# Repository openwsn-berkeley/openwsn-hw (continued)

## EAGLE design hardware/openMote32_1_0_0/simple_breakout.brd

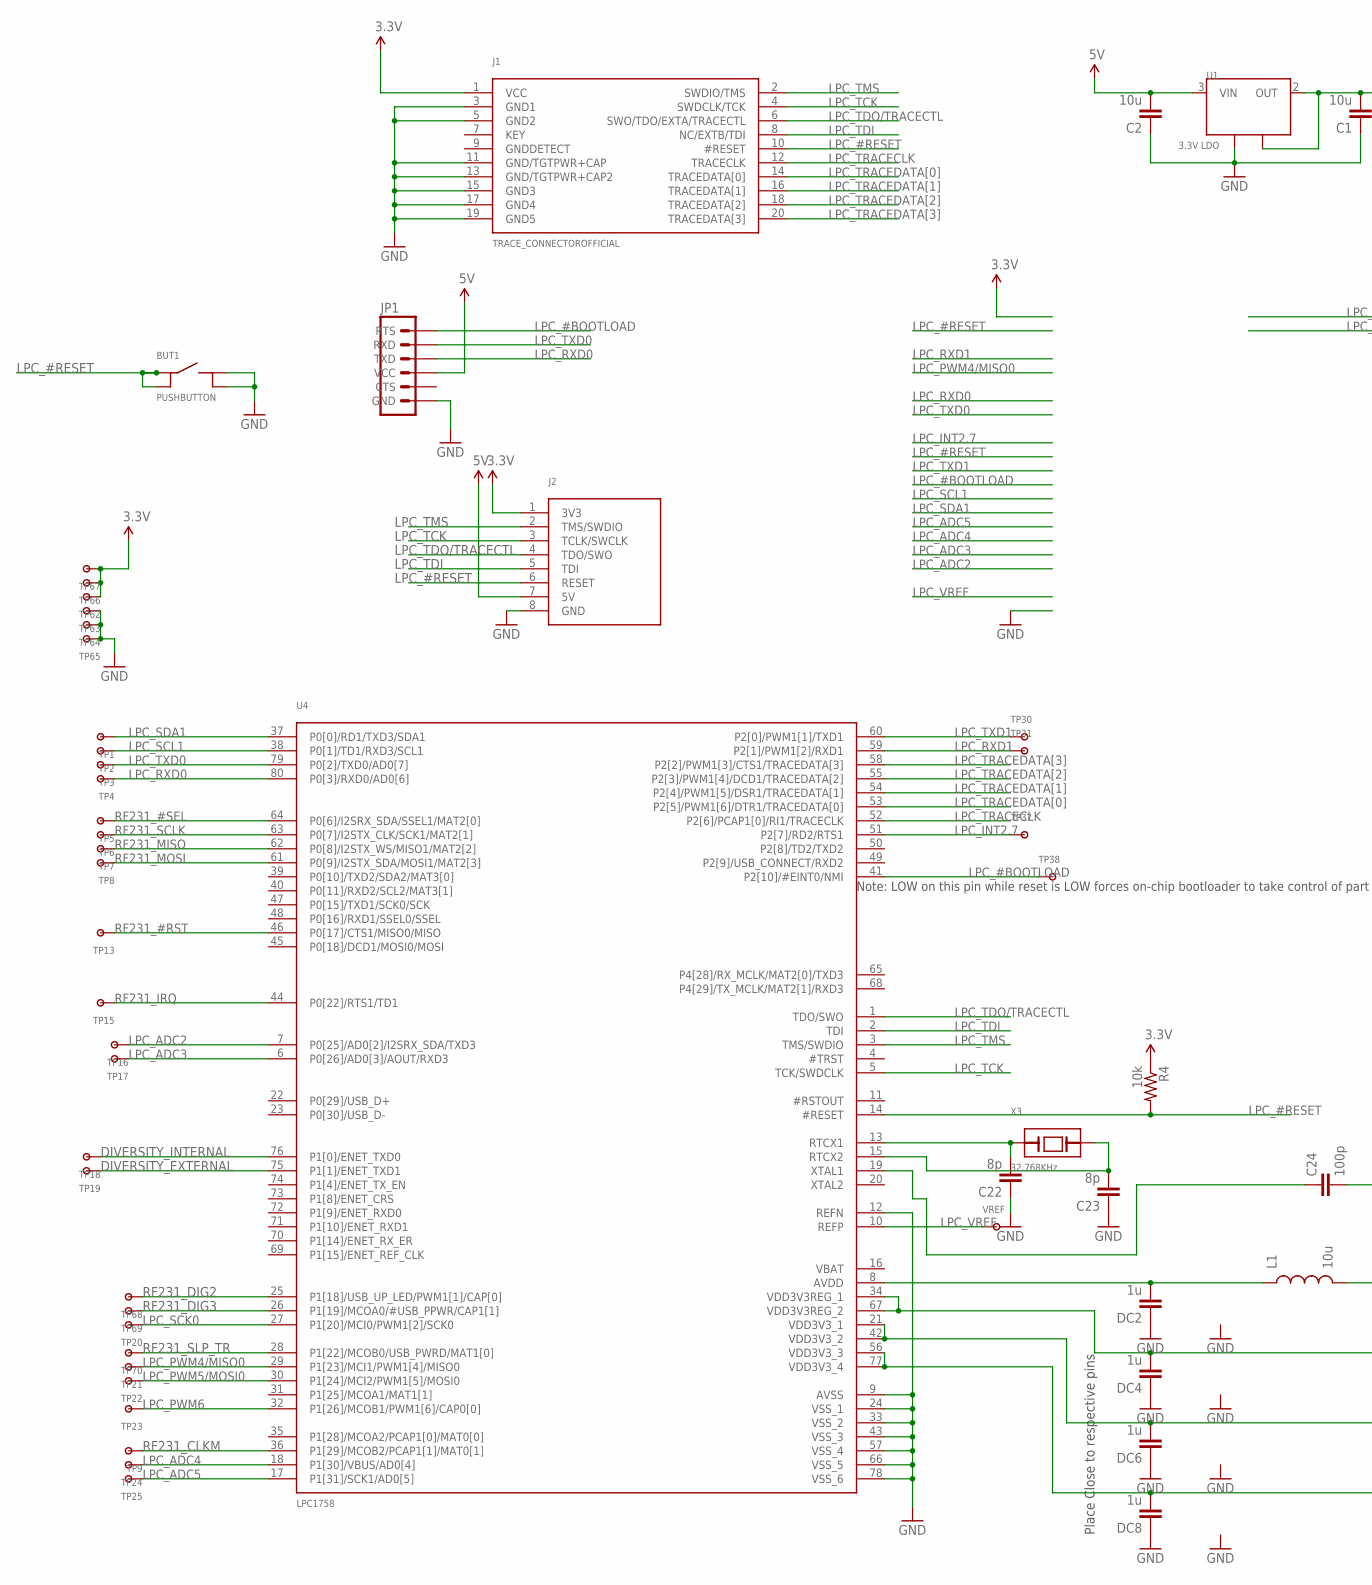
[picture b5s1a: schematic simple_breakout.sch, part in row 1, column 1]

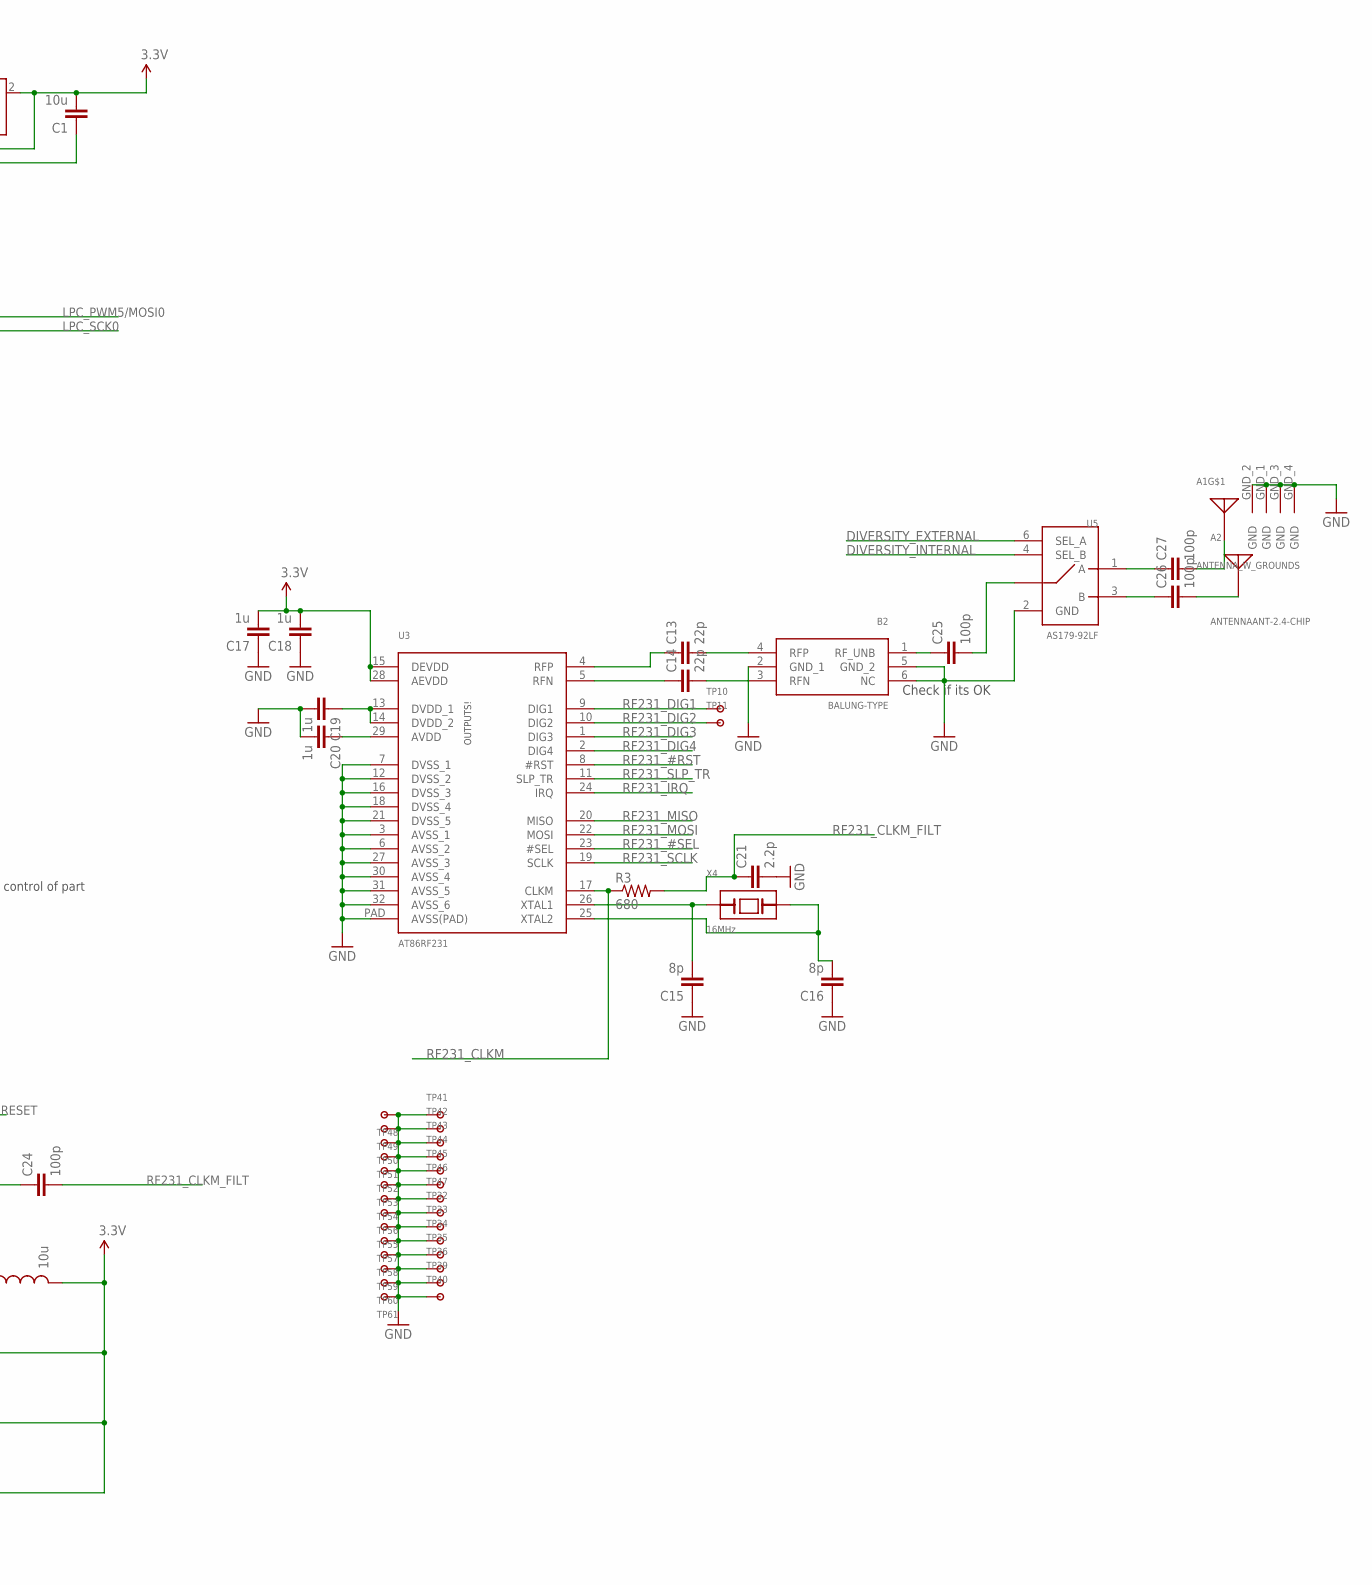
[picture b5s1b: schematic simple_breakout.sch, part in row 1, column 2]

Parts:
A1: ANTENNA_W_GROUNDS; CONREVSMA003.031
A2: ANTENNAANT-2.4-CHIP; ANT-2.4-CHP
B2: BALUNG-TYPE; MURATA_LDB_BALUN
BUT1: PUSHBUTTON; SMT_PUSHBUTTON
C1, C2: 10u; 0805
C13, C14: 22p; C0402
C15, C16, C22, C23: 8p; C0402
C17, C18, C19, C20: 1u; C0402
C21: 2.2p; C0402
C24, C25, C26, C27: 100p; C0402
DC2, DC4, DC6, DC8: 1u; C0402
J1: TRACE_CONNECTOROFFICIAL; FTSH-110-01-L-DV
J2: LPCXPRESSO_JTAG; 1X08
JP1: FTDI_CABLESIP; 1X06
L1: 10u; 0603
R3: 680; C0402
R4: 10k; C0402
TP1, TP2, TP3, TP4, TP5, TP6, TP7, TP8, TP9, TP10, TP11, TP13, TP15, TP16, TP17, TP18, TP19, TP20, TP21, TP22, TP23, TP24, TP25, TP30, TP31, TP37, TP38, TP62, TP63, TP64, TP65, TP66, TP67, TP68, TP69, TP70: TESTPOINT100MIL; TESTPOINT-100MIL
TP32, TP33, TP34, TP35, TP36, TP39, TP40, TP41, TP42, TP43, TP44, TP45, TP46, TP47, TP48, TP49, TP50, TP51, TP52, TP53, TP54, TP55, TP56, TP57, TP58, TP59, TP60, TP61: TESTPOINTSMALLEST; TESTPOINT
U1: 3.3V LDO; SOT223
U3: AT86RF231; ATRF231_32QN2
U4: LPC1758; LPC1758_LQFP80
U5: AS179-92LF; SC-70
VREF: TESTPOINT100MIL; TESTPOINT-100MIL
X3: 32.768KHz; ABS07
X4: 16MHz; CX3225SA

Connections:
3.3V: C1.2, C17.2, C18.2, DC4.2, DC6.2, DC8.2, J1.1 (VCC), J2.1 (3V3), L1.2, R4.1, TP62.2, TP66.2, TP67.2, U1.2 (OUT), U1.4 (TAB), U3.15 (DEVDD), U3.28 (AEVDD), U4.21 (VDD3V3_1), U4.34 (VDD3V3REG_1), U4.42 (VDD3V3_2), U4.56 (VDD3V3_3), U4.67 (VDD3V3REG_2), U4.77 (VDD3V3_4)
5V: C2.2, J2.7 (5V), JP1.3 (VCC), U1.3 (VIN)
DIVERSITY_EXTERNAL: TP19.2, U4.75 (P1[1]/ENET_TXD1), U5.6 (SEL_A)
DIVERSITY_INTERNAL: TP18.2, U4.76 (P1[0]/ENET_TXD0), U5.4 (SEL_B)
GND: A1.GND_1 (GND), A1.GND_2 (GND), A1.GND_3 (GND), A1.GND_4 (GND), B2.2 (GND_1), B2.5 (GND_2), B2.6 (NC), BUT1.2@1 (2), BUT1.2@2 (2), C1.1, C2.1, C15.1, C16.1, C17.1, C18.1, C19.2, C20.2, C21.2, C22.1, C23.1, DC2.1, DC4.1, DC6.1, DC8.1, J1.3 (GND1), J1.5 (GND2), J1.11 (GND/TGTPWR+CAP), J1.13 (GND/TGTPWR+CAP2), J1.15 (GND3), J1.17 (GND4), J1.19 (GND5), J2.8 (GND), JP1.1 (GND), TP32.P$1, TP33.P$1, TP34.P$1, TP35.P$1, TP36.P$1, TP39.P$1, TP40.P$1, TP41.P$1, TP42.P$1, TP43.P$1, TP44.P$1, TP45.P$1, TP46.P$1, TP47.P$1, TP48.P$1, TP49.P$1, TP50.P$1, TP51.P$1, TP52.P$1, TP53.P$1, TP54.P$1, TP55.P$1, TP56.P$1, TP57.P$1, TP58.P$1, TP59.P$1, TP60.P$1, TP61.P$1, TP63.2, TP64.2, TP65.2, U1.1 (GND), U3.3 (AVSS_1), U3.6 (AVSS_2), U3.7 (DVSS_1), U3.12 (DVSS_2), U3.16 (DVSS_3), U3.18 (DVSS_4), U3.21 (DVSS_5), U3.27 (AVSS_3), U3.30 (AVSS_4), U3.31 (AVSS_5), U3.32 (AVSS_6), U3.PAD (AVSS(PAD)), U4.9 (AVSS), U4.12 (REFN), U4.24 (VSS_1), U4.33 (VSS_2), U4.43 (VSS_3), U4.57 (VSS_4), U4.66 (VSS_5), U4.78 (VSS_6), U5.2 (GND)
LPC_#BOOTLOAD: JP1.6 (RTS), TP38.2, U4.41 (P2[10]/#EINT0/NMI)
LPC_#RESET: BUT1.1@1 (1), BUT1.1@2 (1), J1.10 (#RESET), J2.6 (RESET), R4.2, U4.14 (#RESET)
LPC_ADC2: TP16.2, U4.7 (P0[25]/AD0[2]/I2SRX_SDA/TXD3)
LPC_ADC3: TP17.2, U4.6 (P0[26]/AD0[3]/AOUT/RXD3)
LPC_ADC4: TP24.2, U4.18 (P1[30]/VBUS/AD0[4])
LPC_ADC5: TP25.2, U4.17 (P1[31]/SCK1/AD0[5])
LPC_INT2.7: TP37.2, U4.51 (P2[7]/RD2/RTS1)
LPC_PWM4/MISO0: TP21.2, U4.29 (P1[23]/MCI1/PWM1[4]/MISO0)
LPC_PWM5/MOSI0: TP22.2, U4.30 (P1[24]/MCI2/PWM1[5]/MOSI0)
LPC_PWM6: TP23.2, U4.32 (P1[26]/MCOB1/PWM1[6]/CAP0[0])
LPC_RXD0: JP1.4 (TXD), TP4.2, U4.80 (P0[3]/RXD0/AD0[6])
LPC_RXD1: TP31.2, U4.59 (P2[1]/PWM1[2]/RXD1)
LPC_SCK0: TP20.2, U4.27 (P1[20]/MCI0/PWM1[2]/SCK0)
LPC_SCL1: TP2.2, U4.38 (P0[1]/TD1/RXD3/SCL1)
LPC_SDA1: TP1.2, U4.37 (P0[0]/RD1/TXD3/SDA1)
LPC_TCK: J1.4 (SWDCLK/TCK), J2.3 (TCLK/SWCLK), U4.5 (TCK/SWDCLK)
LPC_TDI: J1.8 (NC/EXTB/TDI), J2.5 (TDI), U4.2 (TDI)
LPC_TDO/TRACECTL: J1.6 (SWO/TDO/EXTA/TRACECTL), J2.4 (TDO/SWO), U4.1 (TDO/SWO)
LPC_TMS: J1.2 (SWDIO/TMS), J2.2 (TMS/SWDIO), U4.3 (TMS/SWDIO)
LPC_TRACECLK: J1.12 (TRACECLK), U4.52 (P2[6]/PCAP1[0]/RI1/TRACECLK)
LPC_TRACEDATA[0]: J1.14 (TRACEDATA[0]), U4.53 (P2[5]/PWM1[6]/DTR1/TRACEDATA[0])
LPC_TRACEDATA[1]: J1.16 (TRACEDATA[1]), U4.54 (P2[4]/PWM1[5]/DSR1/TRACEDATA[1])
LPC_TRACEDATA[2]: J1.18 (TRACEDATA[2]), U4.55 (P2[3]/PWM1[4]/DCD1/TRACEDATA[2])
LPC_TRACEDATA[3]: J1.20 (TRACEDATA[3]), U4.58 (P2[2]/PWM1[3]/CTS1/TRACEDATA[3])
LPC_TXD0: JP1.5 (RXD), TP3.2, U4.79 (P0[2]/TXD0/AD0[7])
LPC_TXD1: TP30.2, U4.60 (P2[0]/PWM1[1]/TXD1)
LPC_VREF: U4.10 (REFP), VREF.2
unnamed: B2.3 (RFN), C14.2
unnamed: B2.4 (RFP), C13.2
unnamed: C14.1, U3.5 (RFN)
unnamed: C13.1, U3.4 (RFP)
unnamed: C15.2, U3.26 (XTAL1), X4.3 (A)
unnamed: C16.2, U3.25 (XTAL2), X4.1 (B)
unnamed: C20.1, U3.29 (AVDD)
unnamed: C19.1, U3.13 (DVDD_1), U3.14 (DVDD_2)
unnamed: DC2.2, L1.1, U4.8 (AVDD)
unnamed: C22.2, U4.13 (RTCX1), X3.1 (A)
unnamed: C23.2, U4.15 (RTCX2), X3.2 (B)
unnamed: C24.1, U4.19 (XTAL1)
unnamed: B2.1 (RF_UNB), C25.1
unnamed: C25.2, U5.5 (W)
unnamed: A2.CON, C26.2
unnamed: A1.CON, C27.2
unnamed: C26.1, U5.3 (B)
unnamed: C27.1, U5.1 (A)
RF231_#RST: TP13.2, U3.8 (#RST), U4.46 (P0[17]/CTS1/MISO0/MISO)
RF231_#SEL: TP5.2, U3.23 (#SEL), U4.64 (P0[6]/I2SRX_SDA/SSEL1/MAT2[0])
RF231_CLKM: R3.1, TP9.2, U3.17 (CLKM), U4.36 (P1[29]/MCOB2/PCAP1[1]/MAT0[1])
RF231_CLKM_FILT: C21.1, C24.2, R3.2
RF231_DIG1: TP10.2, U3.9 (DIG1)
RF231_DIG2: TP11.2, TP68.2, U3.10 (DIG2), U4.25 (P1[18]/USB_UP_LED/PWM1[1]/CAP[0])
RF231_DIG3: TP69.2, U3.1 (DIG3), U4.26 (P1[19]/MCOA0/#USB_PPWR/CAP1[1])
RF231_DIG4: U3.2 (DIG4)
RF231_IRQ: TP15.2, U3.24 (IRQ), U4.44 (P0[22]/RTS1/TD1)
RF231_MISO: TP7.2, U3.20 (MISO), U4.62 (P0[8]/I2STX_WS/MISO1/MAT2[2])
RF231_MOSI: TP8.2, U3.22 (MOSI), U4.61 (P0[9]/I2STX_SDA/MOSI1/MAT2[3])
RF231_SCLK: TP6.2, U3.19 (SCLK), U4.63 (P0[7]/I2STX_CLK/SCK1/MAT2[1])
RF231_SLP_TR: TP70.2, U3.11 (SLP_TR), U4.28 (P1[22]/MCOB0/USB_PWRD/MAT1[0])

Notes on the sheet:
Place Close to respective pins
Note: LOW on this pin while reset is LOW forces on-chip bootloader to take control of part
Check if its OK

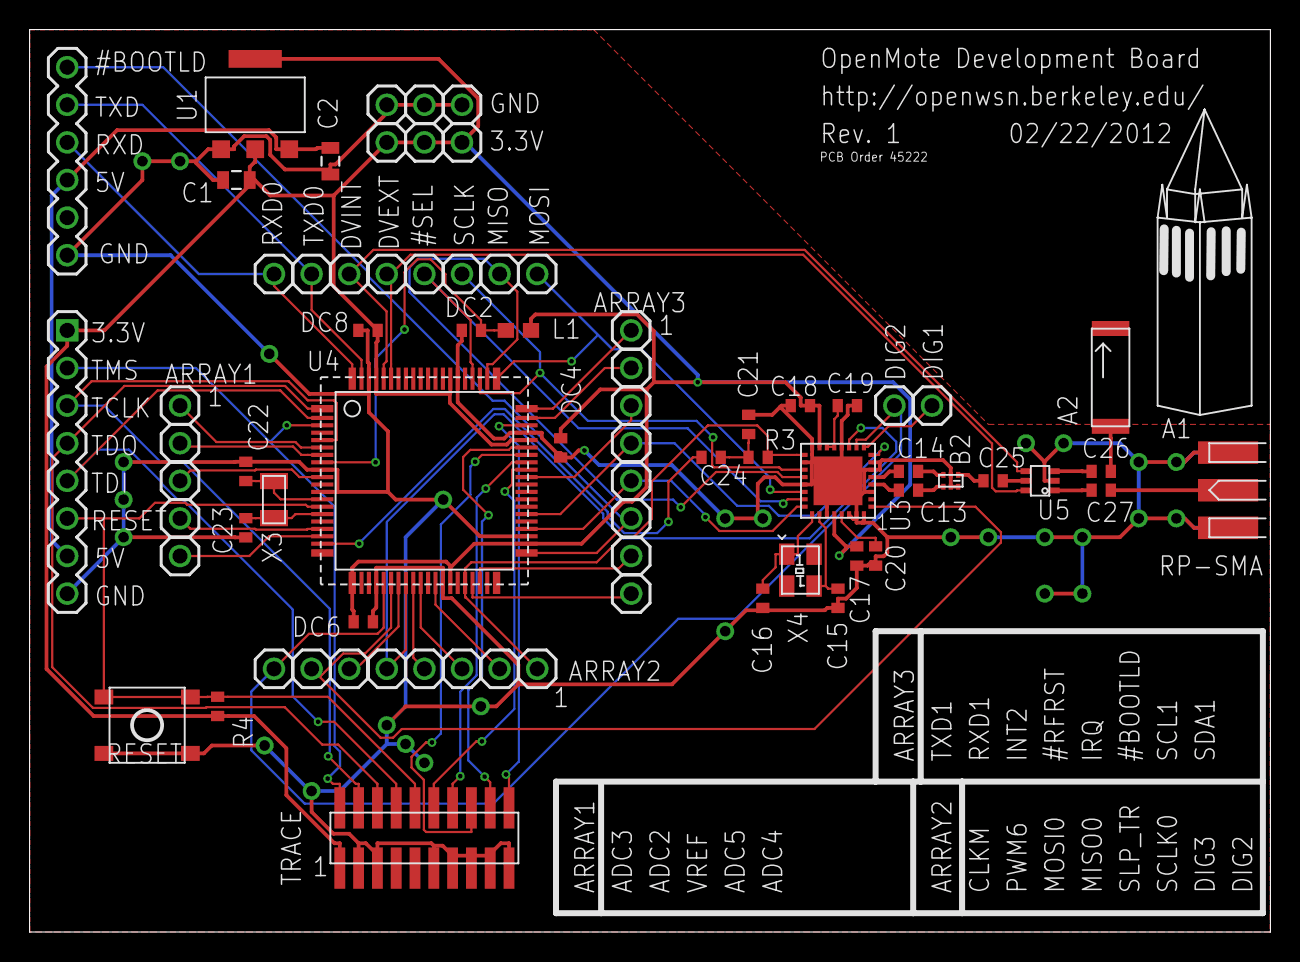
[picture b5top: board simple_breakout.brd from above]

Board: 2 copper layers, 83.8 x 61.0 mm, 103 parts (0 on the bottom side), 62 nets.

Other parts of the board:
TWR: SATHER_TOWER

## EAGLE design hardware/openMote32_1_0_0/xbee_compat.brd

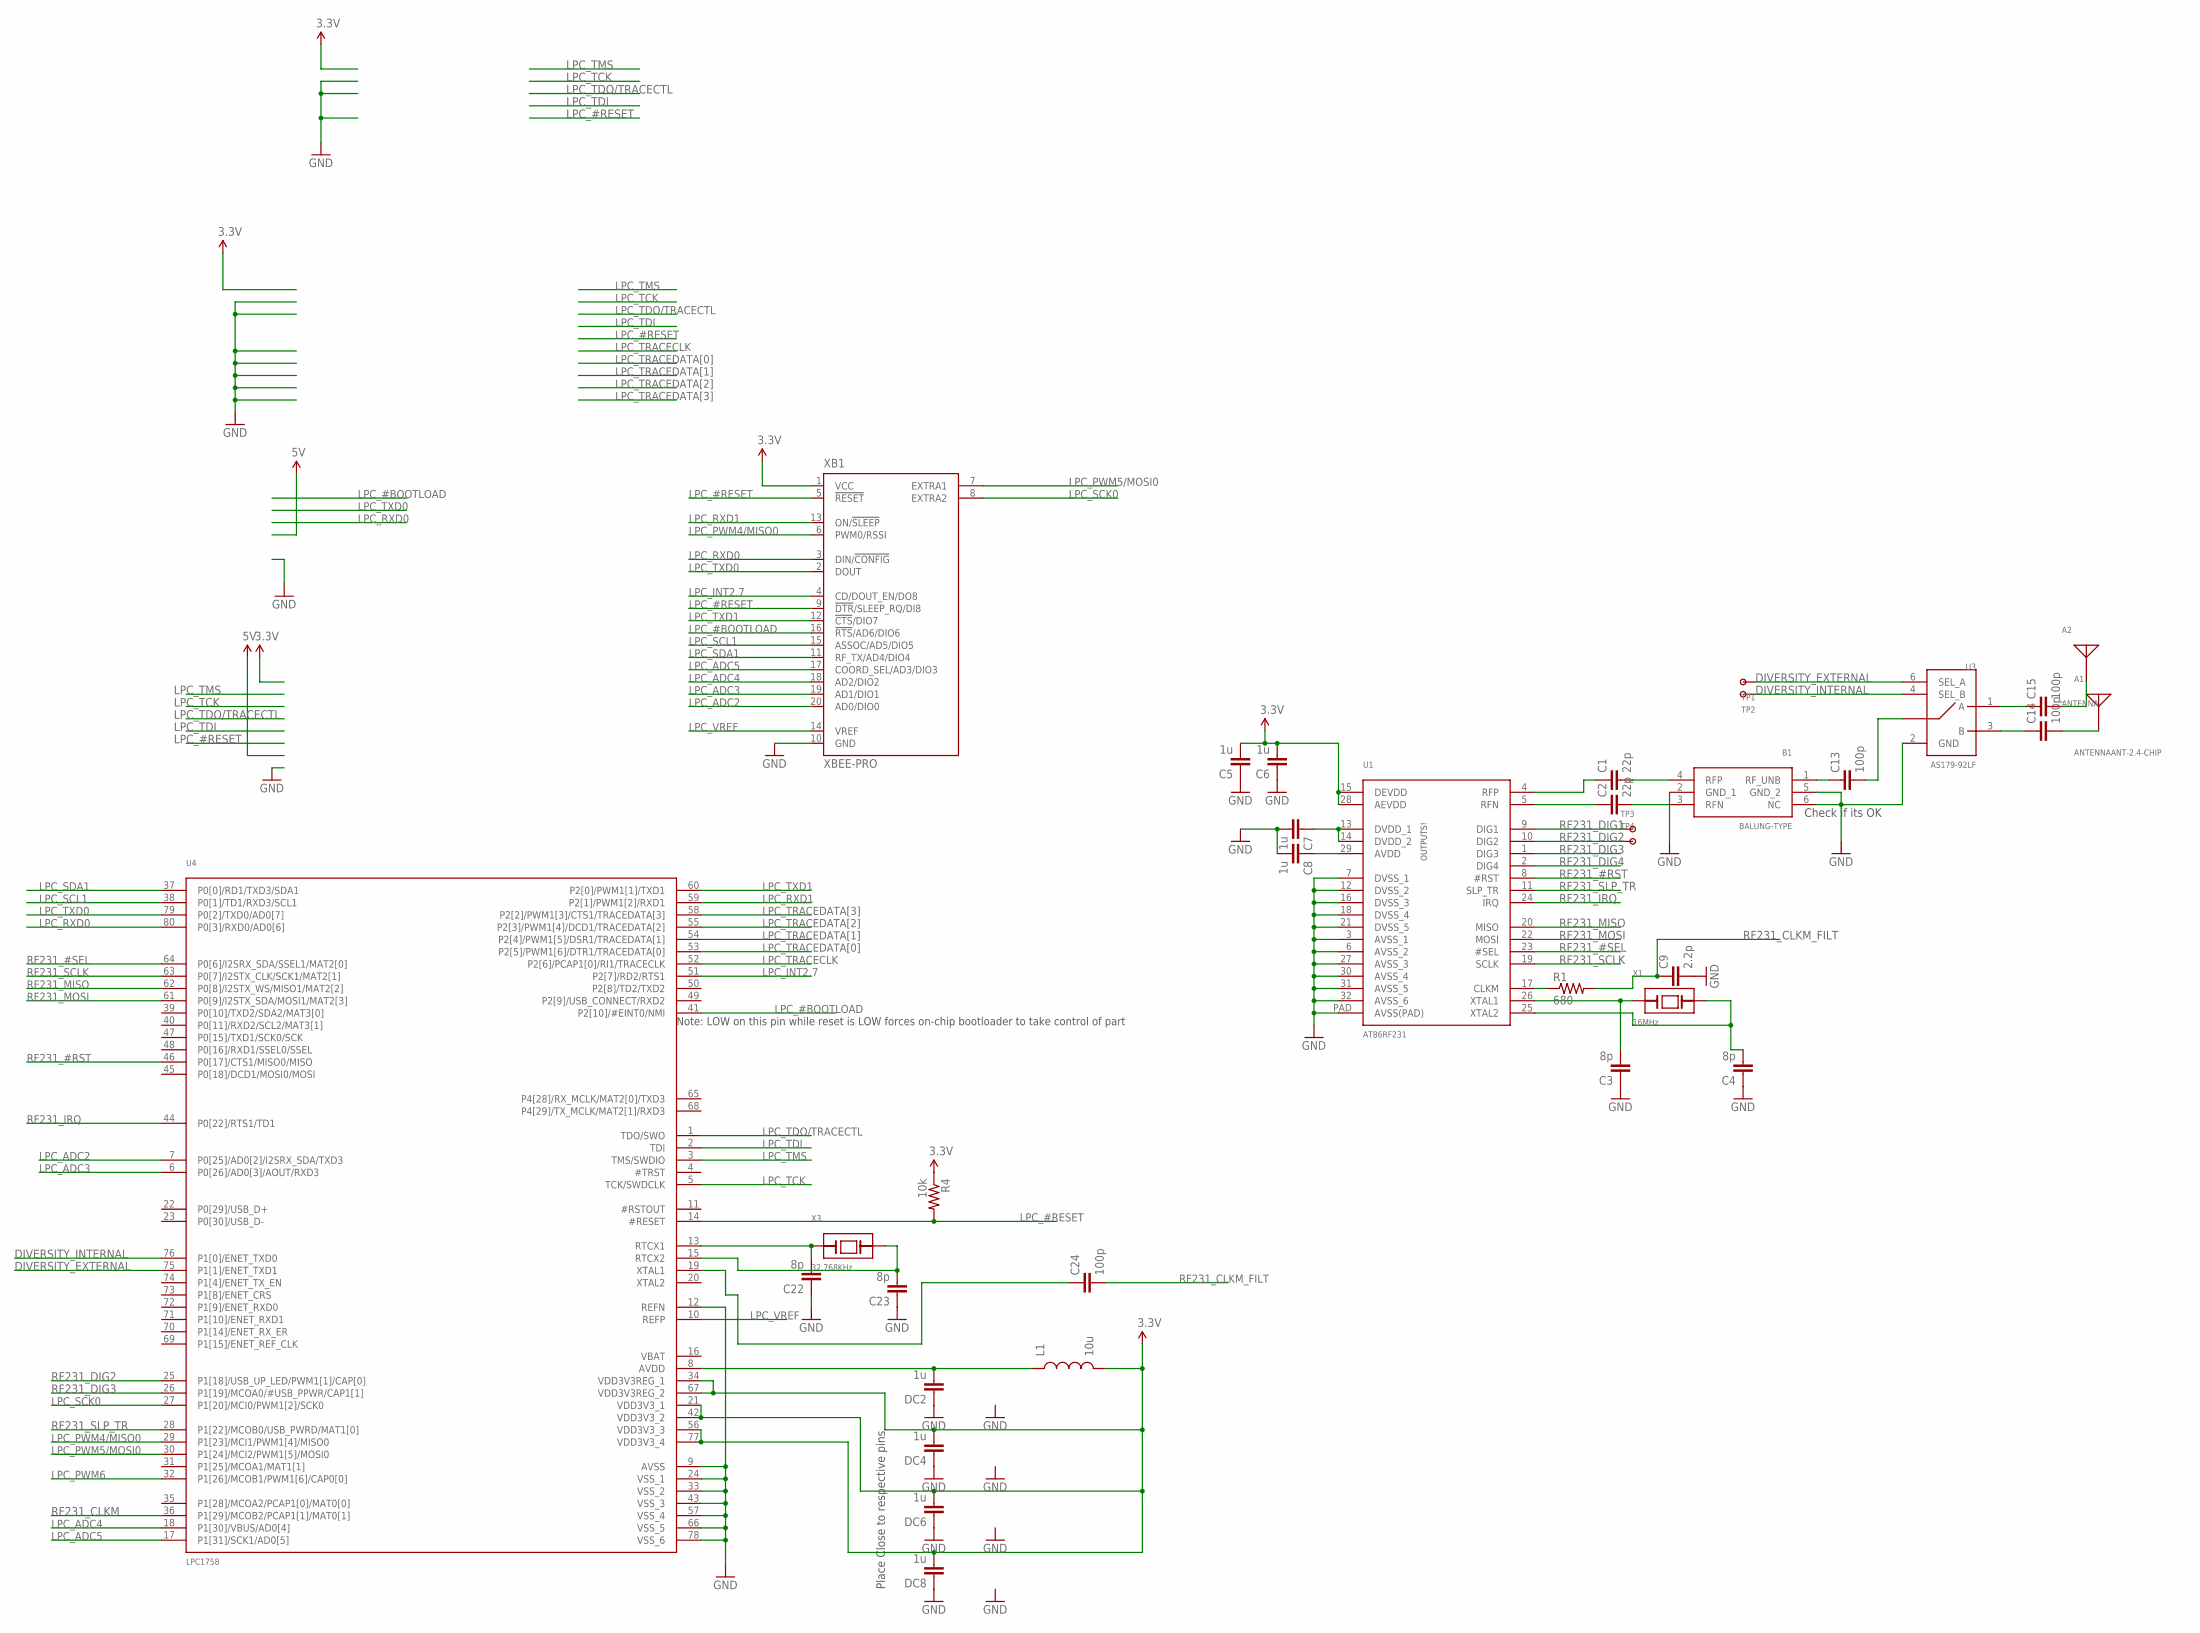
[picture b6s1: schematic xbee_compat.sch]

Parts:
A1: ANTENNAANT-2.4-CHIP; ANT-2.4-CHP
A2: ANTENNA; CONREVSMA003.031
B1: BALUNG-TYPE; MURATA_LDB_BALUN
C1, C2: 22p; C0402
C3, C4, C22, C23: 8p; C0402
C5, C6, C7, C8: 1u; C0402
C9: 2.2p; C0402
C13, C14, C15, C24: 100p; C0402
DC2, DC4, DC6, DC8: 1u; C0402
L1: 10u; 0603
R1: 680; C0402
R4: 10k; C0402
TP1, TP2, TP3, TP4: TESTPOINTSMALLEST; TESTPOINT
U1: AT86RF231; ATRF231_32QN2
U3: AS179-92LF; SC-70
U4: LPC1758; LPC1758_LQFP80
X1: 16MHz; CX3225SA
X3: 32.768KHz; ABS07
XB1: XBEE-PRO

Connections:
3.3V: C5.2, C6.2, DC4.2, DC6.2, DC8.2, L1.2, R4.1, U1.15 (DEVDD), U1.28 (AEVDD), U4.21 (VDD3V3_1), U4.34 (VDD3V3REG_1), U4.42 (VDD3V3_2), U4.56 (VDD3V3_3), U4.67 (VDD3V3REG_2), U4.77 (VDD3V3_4), XB1.1 (VCC)
DIVERSITY_EXTERNAL: TP1.P$1, U3.6 (SEL_A), U4.75 (P1[1]/ENET_TXD1)
DIVERSITY_INTERNAL: TP2.P$1, U3.4 (SEL_B), U4.76 (P1[0]/ENET_TXD0)
GND: B1.2 (GND_1), B1.5 (GND_2), B1.6 (NC), C3.1, C4.1, C5.1, C6.1, C7.2, C8.2, C9.2, C22.1, C23.1, DC2.1, DC4.1, DC6.1, DC8.1, U1.3 (AVSS_1), U1.6 (AVSS_2), U1.7 (DVSS_1), U1.12 (DVSS_2), U1.16 (DVSS_3), U1.18 (DVSS_4), U1.21 (DVSS_5), U1.27 (AVSS_3), U1.30 (AVSS_4), U1.31 (AVSS_5), U1.32 (AVSS_6), U1.PAD (AVSS(PAD)), U3.2 (GND), U4.9 (AVSS), U4.12 (REFN), U4.24 (VSS_1), U4.33 (VSS_2), U4.43 (VSS_3), U4.57 (VSS_4), U4.66 (VSS_5), U4.78 (VSS_6), XB1.10 (GND)
LPC_#BOOTLOAD: U4.41 (P2[10]/#EINT0/NMI), XB1.16 (!RTS!/AD6/DIO6)
LPC_#RESET: R4.2, U4.14 (#RESET), XB1.5 (!RESET), XB1.9 (!DTR!/SLEEP_RQ/DI8)
LPC_ADC2: U4.7 (P0[25]/AD0[2]/I2SRX_SDA/TXD3), XB1.20 (AD0/DIO0)
LPC_ADC3: U4.6 (P0[26]/AD0[3]/AOUT/RXD3), XB1.19 (AD1/DIO1)
LPC_ADC4: U4.18 (P1[30]/VBUS/AD0[4]), XB1.18 (AD2/DIO2)
LPC_ADC5: U4.17 (P1[31]/SCK1/AD0[5]), XB1.17 (COORD_SEL/AD3/DIO3)
LPC_INT2.7: U4.51 (P2[7]/RD2/RTS1), XB1.4 (CD/DOUT_EN/DO8)
LPC_PWM4/MISO0: U4.29 (P1[23]/MCI1/PWM1[4]/MISO0), XB1.6 (PWM0/RSSI)
LPC_PWM5/MOSI0: U4.30 (P1[24]/MCI2/PWM1[5]/MOSI0), XB1.7 (EXTRA1)
LPC_PWM6: U4.32 (P1[26]/MCOB1/PWM1[6]/CAP0[0])
LPC_RXD0: U4.80 (P0[3]/RXD0/AD0[6]), XB1.3 (DIN/!CONFIG)
LPC_RXD1: U4.59 (P2[1]/PWM1[2]/RXD1), XB1.13 (ON/!SLEEP)
LPC_SCK0: U4.27 (P1[20]/MCI0/PWM1[2]/SCK0), XB1.8 (EXTRA2)
LPC_SCL1: U4.38 (P0[1]/TD1/RXD3/SCL1), XB1.15 (ASSOC/AD5/DIO5)
LPC_SDA1: U4.37 (P0[0]/RD1/TXD3/SDA1), XB1.11 (RF_TX/AD4/DIO4)
LPC_TCK: U4.5 (TCK/SWDCLK)
LPC_TDI: U4.2 (TDI)
LPC_TDO/TRACECTL: U4.1 (TDO/SWO)
LPC_TMS: U4.3 (TMS/SWDIO)
LPC_TRACECLK: U4.52 (P2[6]/PCAP1[0]/RI1/TRACECLK)
LPC_TRACEDATA[0]: U4.53 (P2[5]/PWM1[6]/DTR1/TRACEDATA[0])
LPC_TRACEDATA[1]: U4.54 (P2[4]/PWM1[5]/DSR1/TRACEDATA[1])
LPC_TRACEDATA[2]: U4.55 (P2[3]/PWM1[4]/DCD1/TRACEDATA[2])
LPC_TRACEDATA[3]: U4.58 (P2[2]/PWM1[3]/CTS1/TRACEDATA[3])
LPC_TXD0: U4.79 (P0[2]/TXD0/AD0[7]), XB1.2 (DOUT)
LPC_TXD1: U4.60 (P2[0]/PWM1[1]/TXD1), XB1.12 (!CTS!/DIO7)
LPC_VREF: U4.10 (REFP), XB1.14 (VREF)
unnamed: B1.3 (RFN), C2.2
unnamed: B1.4 (RFP), C1.2
unnamed: B1.1 (RF_UNB), C13.1
unnamed: C2.1, U1.5 (RFN)
unnamed: C1.1, U1.4 (RFP)
unnamed: C3.2, U1.26 (XTAL1), X1.3 (A)
unnamed: C4.2, U1.25 (XTAL2), X1.1 (B)
unnamed: C8.1, U1.29 (AVDD)
unnamed: C7.1, U1.13 (DVDD_1), U1.14 (DVDD_2)
unnamed: R1.1, U1.17 (CLKM)
unnamed: C13.2, U3.5 (W)
unnamed: C14.1, U3.3 (B)
unnamed: C15.1, U3.1 (A)
unnamed: A1.CON, C14.2
unnamed: A2.CON, C15.2
unnamed: DC2.2, L1.1, U4.8 (AVDD)
unnamed: C22.2, U4.13 (RTCX1), X3.1 (A)
unnamed: C23.2, U4.15 (RTCX2), X3.2 (B)
unnamed: C24.1, U4.19 (XTAL1)
RF231_#RST: U1.8 (#RST), U4.46 (P0[17]/CTS1/MISO0/MISO)
RF231_#SEL: U1.23 (#SEL), U4.64 (P0[6]/I2SRX_SDA/SSEL1/MAT2[0])
RF231_CLKM: U4.36 (P1[29]/MCOB2/PCAP1[1]/MAT0[1])
RF231_CLKM_FILT: C9.1, C24.2, R1.2
RF231_DIG1: TP3.P$1, U1.9 (DIG1)
RF231_DIG2: TP4.P$1, U1.10 (DIG2), U4.25 (P1[18]/USB_UP_LED/PWM1[1]/CAP[0])
RF231_DIG3: U1.1 (DIG3), U4.26 (P1[19]/MCOA0/#USB_PPWR/CAP1[1])
RF231_DIG4: U1.2 (DIG4)
RF231_IRQ: U1.24 (IRQ), U4.44 (P0[22]/RTS1/TD1)
RF231_MISO: U1.20 (MISO), U4.62 (P0[8]/I2STX_WS/MISO1/MAT2[2])
RF231_MOSI: U1.22 (MOSI), U4.61 (P0[9]/I2STX_SDA/MOSI1/MAT2[3])
RF231_SCLK: U1.19 (SCLK), U4.63 (P0[7]/I2STX_CLK/SCK1/MAT2[1])
RF231_SLP_TR: U1.11 (SLP_TR), U4.28 (P1[22]/MCOB0/USB_PWRD/MAT1[0])

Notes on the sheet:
Check if its OK
Place Close to respective pins
Note: LOW on this pin while reset is LOW forces on-chip bootloader to take control of part

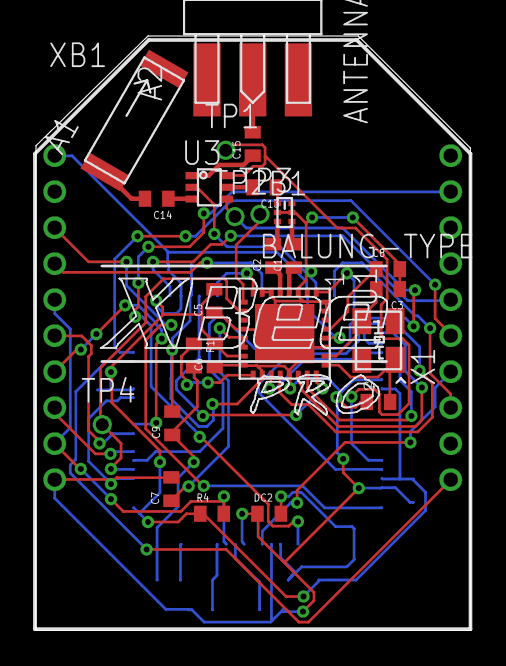
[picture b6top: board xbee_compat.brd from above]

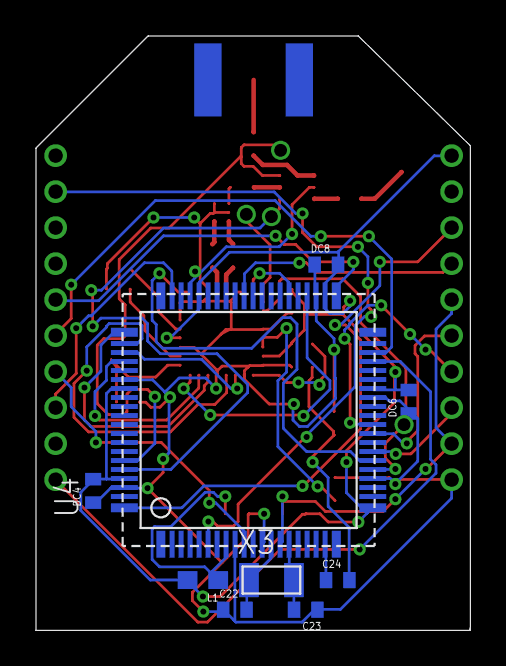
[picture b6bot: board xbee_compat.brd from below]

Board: 2 copper layers, 24.1 x 33.0 mm, 35 parts (9 on the bottom side), 51 nets.

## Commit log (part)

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2012-05-11 implemented some pending methods.
2012-05-12 completed some of the methods pending in lptmr for ez430
2012-05-12 modified radiotimer to keep previous timeout.
    not working correctly yet.
2012-05-13 changes to radiotimer example application: fire multiple times in a slot
2012-05-13 Fixing lptimer. 01bsp_radiotimer_alt for GINA.
2012-05-13 moving files around (WIP)
2012-05-13 renaming
2012-05-13 temp
2012-05-13 creating common abstimer module (WIP)
2012-05-13 removing alt_timers/ directory
2012-05-13 adding sctimer module for eZ430. Fixed related IAR projects.
2012-05-13 adding (dummy) 01bsp_bsp_timer_alt application for GINA
2012-05-13 adding 01bsp_bsp_timer_alt application for GINA
2012-05-13 both_timer applications for GINA
2012-05-13 handle interrupts firing at the same time in abstimer.c
2012-05-14 abstimer.c now handles close timers
2012-05-14 cleaning up all GINA projects
2012-05-14 indentation
2012-05-14 removing eui64 application from eZ430 workspace
2012-05-14 Adding closetimers applications to eZ430
2012-05-14 adding 02drv_opentimers_alt application to eZ430's workspace
2012-05-14 adding debugpins application to GINA workspace
2012-05-14 ignore list
2012-05-14 added callback in sctimer
2012-05-14 k20 sctimer tested. slight modification in abstimer cleaning of opentimers.
2012-05-15 removed unused import.
2012-05-15 uart working
2012-05-15 eui module added. some cleaning in other files.
2012-05-15 comments added.
2012-05-15 not needed anymore. Old version of what it is in xpressohack
2012-05-15 Not needed anymore. Old testing example.
2012-05-16 remove registers from PC port
2012-05-16 implement missing bsp_timer function for PC port
2012-05-16 remove unnecessary include
2012-05-16 emulated bsp_timer
2012-05-16 working bsp_timer emulation
2012-05-16 working closetimers emulation
2012-05-16 working debugpins emulation
2012-05-17 Added radio pins and configured radio external isr.
2012-05-17 comments
2012-05-17 cleaner implemetation of bsp_timer
2012-05-17 Fixing flawed login in timeline management
2012-05-17 Fixing recursivity issue
2012-05-17 SPI working
2012-05-18 radio working. changed slptr pin because it was conflicting with one spi pin.
2012-05-18 corrected variable declaration inside if statement. placed them at the beginning of the function
2012-05-19 changed debugpins
2012-05-19 cleaning initialization of modules
2012-05-19 adding some basic bsp test projects for codewarrior
2012-05-20 better management of mote concurrency
2012-05-20 PC library for openos
2012-05-20 SCons environment for stack (WIP)
2012-05-20 creating dirs for CLI and GUI interface
2012-05-20 moving SimCli to separate directory
2012-05-20 adding a boot delay
2012-05-20 working propagation module in emulated code
2012-05-20 removing unnecessary assert() statements
2012-05-21 OpenWSN application builds for emulator
2012-05-22 cleaner handoff between radio and radiotimer modules
2012-05-22 return real address
2012-05-22 fixing radio emulation
2012-05-22 changing default DAGroot mote
2012-05-22 cleaner eui64 logging
2012-05-23 changed one debugpin slight modifications in abstimers.
2012-05-23 a ; was missing.
2012-05-23 working OpenWSN example. GUI skeleton.
2012-05-23 simulator: ugly as hell, but it works :)
2012-05-24 adding missing include
2012-05-24 fixing wrong signature
2012-05-24 clear isr function in sctimer for gina
    other abstimer tunning .. (WIP)
2012-05-25 debug traces everywhere. trying to find the bug. WIP)
2012-05-25 alternative openwsn project for GINA
2012-05-25 removed unused variable
2012-05-25 making alternative openwsn project for GINA
2012-05-25 test to find the bug in abstimers
2012-05-28 another implementation of abstimers .. needs to be tested with gina.
2012-05-29 (WIP) some debug added..
2012-05-31 trying svn:ignore to nuke current_monitor.X
2012-06-10 updated gologic trace for 2 motes
2012-06-10 changing default MASTER
2012-06-10 updating bothtimers and closetimers for GINA
2012-06-11 All k20 refactoring, bsp, and extended bsp functions
2012-06-11 Initial import.
2012-06-11 moving #include "string.h" to board_info to make platforms toolchain independent.
    correcting includes in corresponding files.
2012-06-11 making path relative to workspace
2012-06-13 gina and telosb range tests projects
2012-06-13 use HW for closetimers project, not simulator
2012-06-13 wiggle ISR pin tin TIMER_A interrupt
2012-06-13 load period-1 in radiotimer
2012-06-13 cleaner interrupt handling in abstimer.c
2012-06-14 software reset and other minor changes.
2012-06-15 Adding derfmega project (Files are linked to main openwsn files, but directories cannot be linked)
2012-06-15 Adding k20 mote
2012-06-15 minor correction on button configuration
2012-06-16 Add derfmega BSP
2012-06-16 derfmega project file change
2012-06-18 setting isr button as input.
2012-06-20 Adding energy harvesting reports, as requested by Vincent Lee.
2012-06-21 Openmote v2 changes
2012-06-21 Openmote v2 changes+
2012-06-21 added hdlcserial block that sits between uart drivers and the application wishing to speak over uart. still needs debugging and testing
2012-06-21 fixed callback issues. Code compiles and links (after moving variables to .c file). There is an issue with interrupts which is being resolved.
2012-06-23 moved variable declaration at the beginning of each function. Other compilers out of IAR doesn't support variable declaration in the middle of a function.
2012-06-23 annotated datasheet
2012-06-23 updated updated ISR_DELAY for close timers
2012-06-23 enable NMI flash violation interrupt. disable button.
2012-06-23 clear debugpins at initialization
2012-06-24 capture wrong radio IRQ status
2012-06-24 add INTERRUPT_DECLARATION to scheduler.c
2012-06-24 add INTERRUPT_DECLARATION to IEEE802154E.c
2012-06-24 add INTERRUPT_DECLARATION to schedule.c
2012-06-24 add INTERRUPT_DECLARATION to openqueue.c
2012-06-24 cleaned up moteProbe
2012-06-24 splitting moteProbe into files and classes
2012-06-24 logging in moteProbe
2012-06-24 more logging
2012-06-24 adding folder for moteConnector
2012-06-24 moving moteConnector module to its directory
2012-06-24 moving files
2012-06-24 removing unused folder
2012-06-24 adding moteState module
2012-06-24 adding generic Parser object
2012-06-25 parsing with struct
2012-06-25 adding 3d pictures of the openmote.
2012-06-26 added hdlc to moteprobeserial; still needs testing
2012-06-27 parsing status messages
2012-06-27 complete parsing of status messages, and creation of named tuples on-the-fly
2012-06-27 storing state in moteState
2012-06-27 removing unused methods
2012-06-27 Modified version of frame format only DIO and DAO has been modified according to RFC 6550
2012-06-27 Added function get all neighbor table and schedule table were a pointer is being returned which must be used in reading the tables only!
2012-06-27 layerdebug is an application to be used to debug a certain layer in which you need to include the layer that you want to debug. From there you can send the information that you want to collect. So fa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
2012-06-28 k20 bootloader codewarrior project
2012-06-30 added rsvp headers and some constants defined at openwsn.h
2012-06-30 switch on more logging
2012-06-30 handler for 'internals' command
2012-06-30 cleaner module initialization
2012-06-30 fixing wrong name printing error
2012-06-30 quit procedure
2012-07-01 moteProbeCli application
2012-07-01 update ignore list
2012-07-01 list available elems
2012-07-01 generic printing of StateElem objects
2012-07-01 #define'ing the mote states
2012-07-01 changing 'internals' command to 'info'
2012-07-01 queuing between moteConnector and MoteConnectorConsumer
2012-07-01 pretty printing for moteState subclasses
2012-07-02 state objects contain 'meta' and 'data' attributes
2012-07-02 creating a moteStateGui application (WIP)
2012-07-02 fixing grid issue in OpenTable
2012-07-02 moteStateGui displays Asn
2012-07-02 display more states
2012-07-02 functional mote state GUI
2012-07-02 cleaner organization of the GUI elements
2012-07-02 fixing parsing of schedule row
2012-07-02 cleaner display
2012-07-02 handler parsing error correctly
2012-07-02 updated GINA OpenWSN project to add the layerdebug module
2012-07-03 revert HDLC implementation in moteProbe. Waiting for Fabien to test before putting it in trunk.
2012-07-03 sensor initialization
2012-07-03 committing openvisualizer svn version 1817, as backup until new OpenVisualizer works
2012-07-03 better try/except'ing during parsing
2012-07-03 adding UDP rand application
2012-07-03 writing raw data to csv file
2012-07-04 bug fixed. ENABLE_INTERRUPTS required before return. Thanks to one of openWSN users for finding that.
2012-07-04 openTypes (WIP)
2012-07-04 cleaner logging
2012-07-04 openType and typeAsn to better represent internal OpenWSN types
2012-07-04 more typeAddr
2012-07-05 typeCelltype
2012-07-05 typeComponent
2012-07-05 more moteState
2012-07-05 correct ordering of ASN
2012-07-05 turning bytes into addresses
2012-07-05 fixing struct orderings
2012-07-05 fixing assert error
2012-07-05 type RSSI
2012-07-05 simpler __str__ methods
2012-07-05 OpenFrameLbr
2012-07-05 code cleaning
2012-07-06 modifications and minor corrections on layerdebug.c
2012-07-06 openqueue flush on desynch. solves non-synchronizing bug when openqueue is full. getfreepacketbuffer from queue not enabled for layers higher than mac when desynch. getfreepacketbuffer sets the owner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
2012-07-06 circular array to debug asnOffset. will be removed after verification.
2012-07-07 method to JSONify the state elements
2012-07-07 removing unused UI elements
2012-07-08 fixing bug in help info printing
2012-07-08 remove unused files
2012-07-08 adding callback to OpenFrameLbr
2012-07-08 removing all Tkinter garbage from lbrClient
2012-07-08 refactoring lbrClient
2012-07-08 successful connection to LBR
2012-07-08 implementing ParserData
2012-07-08 new openVisualizer now connects to the LBR
2012-07-08 moving files around
2012-07-08 removing openVisualizer/ dir
2012-07-09 EndPoint skeleton (WIP)
2012-07-09 little fixes (WIP)
2012-07-09 fix recursive instantiation (oops!)
2012-07-09 renaming module
2012-07-09 fixing sleep units
2012-07-09 working example
2012-07-09 adding endPointUdpRaw application which prints UDP payload on screen (no CoAP parsing)
2012-07-09 cleaner timestamp formatting when printing
2012-07-09 old/ dir for older parsing file (to be remove when CoAP parsing completed)
2012-07-09 removing unused directory
2012-07-09 skeleton for publishing data as web service
2012-07-09 renaming (WIP)
2012-07-09 EpTestWeb application
2012-07-09 Google Gauge display of last data (WIP)
2012-07-09 removing unused dir
2012-07-09 adding cli program to test the reservation protocol
2012-07-10 remove log files
2012-07-10 minor corrections on JSONWrapper and CoapHeader&Payload.
2012-07-10 remove test file
2012-07-10 test to be removed
2012-07-10 revised channel hopping
2012-07-11 Specific Parser and Factory. (WIP)
2012-07-11 debug structure for channel hopping added
    some typos corrected
2012-07-11 small changes. (WIP)
2012-07-11 a temporary debugging app
2012-07-13 SpecificParser for layerdebug and logging at openvisualizer/lbrClient/lbrClient.py
2012-07-13 minor corrections and some debugging. __subclasses__ does not work with SpecificParser but works with Parser.??
2012-07-13 minor changes to facilitate debug.
2012-07-14 remove padding bids in ParserStatus
2012-07-14 adding code to pack network and serial structs.
2012-07-16 packing open_address
2012-07-17 ensuring that only one filehandler per data stream is added to the logger.
2012-07-17 cleaning code
2012-10-22 add back hardware commits part 1 of 3
2012-10-22 add back hardware commits part 2 of 3
2012-10-22 add back hardware commits part 3.2 of 3
2012-10-22 add back hardware commits part 3.last of 3
2012-12-04 Added openmote32_2_0_1 with fixes
2012-12-04 Added BOM
2013-03-22 update schematic of OpenMoteSTM
2013-03-22 pcb and schematic files of Altium Designer
2013-05-04 added a test pad and generated gerbers; modified BOM for cc2533, but cc2541 works (drop-in)
2013-08-05 fixing the LEDs in the BOM
2014-01-21 adding gerbers and renaming folder
2014-01-21 deleting wrong dir
